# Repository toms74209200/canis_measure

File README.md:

<h1 style="text-align: center; margin-bottom: 4rem;">
<p style="font-size: 3rem;">Canis Measure</p>
Air Quality Monitor
</h1>

https://github.com/user-attachments/assets/3cffaff6-82ad-4612-b39e-0665e6a29b27

## Features

### Temperature and Humidity

Temperature and humidity sensor is the SHT30.

### Pressure, CO2

Pressure sensor is the BMP280, CO2 sensor is the MH-Z19B.

## Specification

- [Espressif ESP32-C6](https://www.espressif.com/en/products/socs/esp32-c6)
- [Sensirion SHT30](https://sensirion.com/products/catalog/SHT30-DIS-B)
- [BOSCH BMP280](https://www.bosch-sensortec.com/products/environmental-sensors/pressure-sensors/bmp280/)
- [Winsen MH-Z19B](https://www.winsen-sensor.com/product/mh-z19b.html)
- 128x64 OLED display(SSD1306)

### Schematic

https://github.com/toms74209200/canis_measure/blob/master/pcb/EAQM-250201.pdf

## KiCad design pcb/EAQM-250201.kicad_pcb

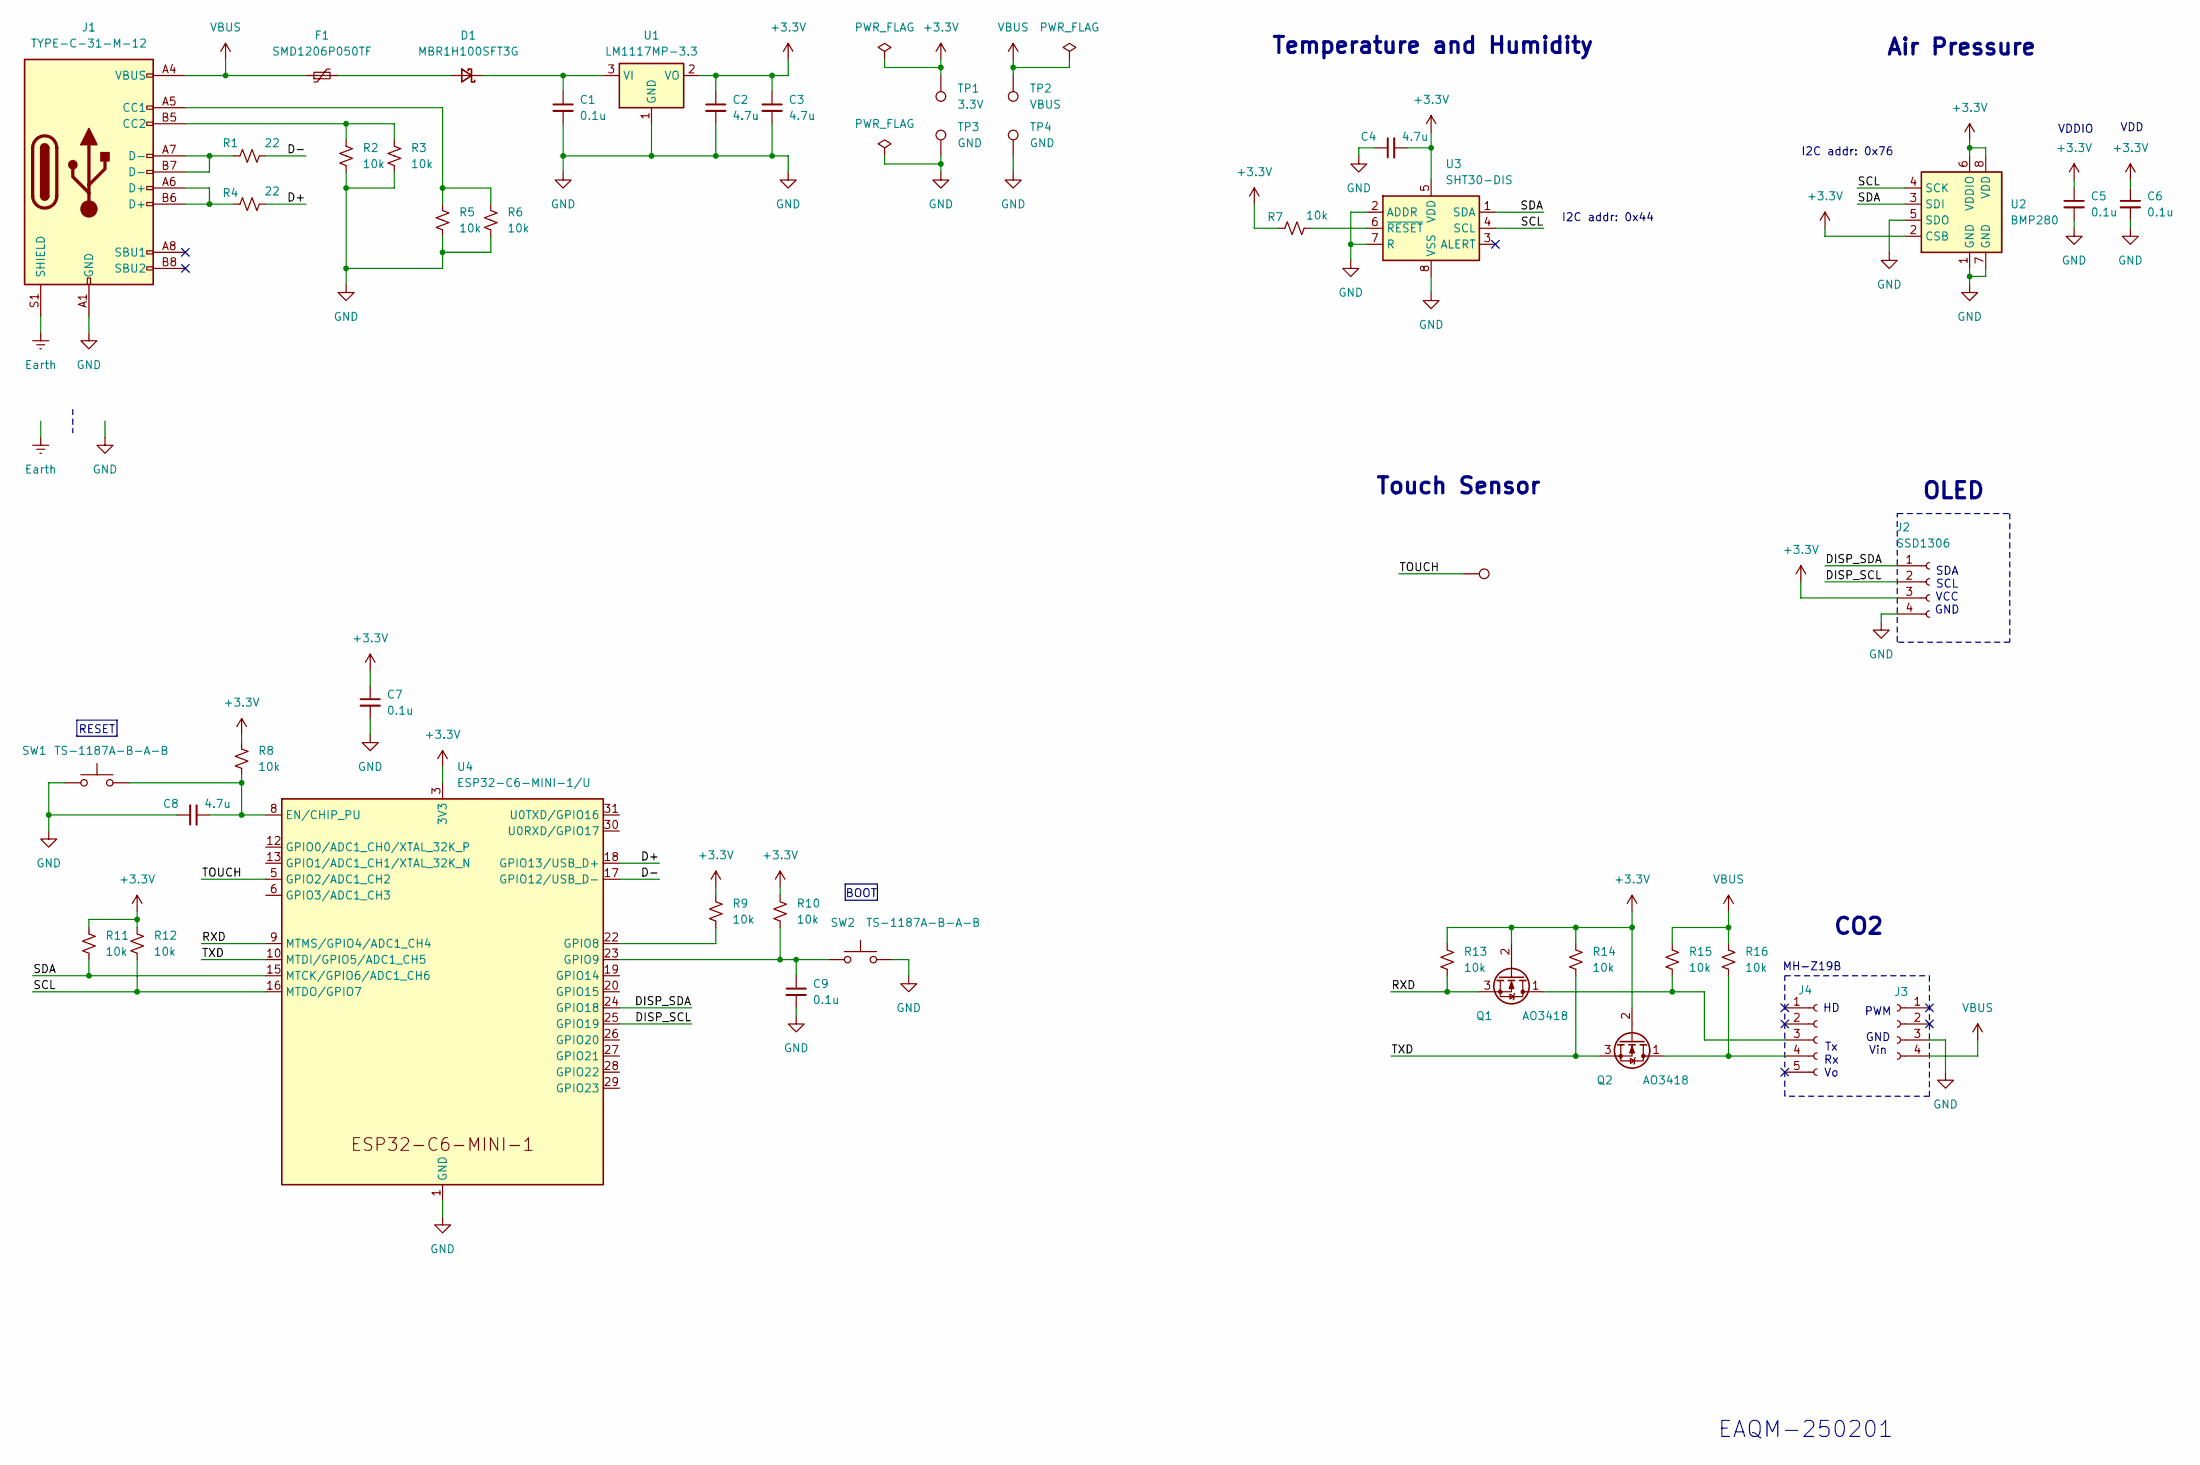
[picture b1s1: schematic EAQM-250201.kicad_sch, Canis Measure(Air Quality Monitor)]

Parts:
C1, C5, C6, C7, C9: 0.1u; C_0603_1608Metric
C2, C3, C4, C8: 4.7u; C_0603_1608Metric
D1: MBR1H100SFT3G; D_SOD-123F
F1: SMD1206P050TF; Fuse_1206_3216Metric
J1: TYPE-C-31-M-12; USB_C_Receptacle_Palconn_UTC16-G
J2: SSD1306; PinHeader_1x04_P2.54mm_Vertical
J3: Conn_01x04_Socket; PinHeader_1x04_P2.54mm_Vertical
J4: Conn_01x05_Socket; PinHeader_1x05_P2.54mm_Vertical
Q1, Q2: AO3418; SOT-23-3
R1, R4: 22; R_0603_1608Metric
R2, R3, R5, R6, R7, R8, R9, R10, R11, R12, R13, R14, R15, R16: 10k; R_0603_1608Metric
SW1, SW2: TS-1187A-B-A-B; SW_Push_1P1T_XKB_TS-1187A
TP1: 3.3V; TestPoint_Pad_D1.0mm
TP2: VBUS; TestPoint_Pad_D1.0mm
TP3, TP4: GND; TestPoint_Pad_D1.0mm
TP5: TestPoint
U1: LM1117MP-3.3; SOT-223-3_TabPin2
U2: BMP280; Bosch_LGA-8_2x2.5mm_P0.65mm_ClockwisePinNumbering
U3: SHT30-DIS; Sensirion_DFN-8-1EP_2.5x2.5mm_P0.5mm_EP1.1x1.7mm
U4: ESP32-C6-MINI-1/U; ESP32-C6-MINI-1

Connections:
+3.3V: C2.1, C3.1, C4.2, C5.1, C6.1, C7.1, J2.3, Q1.2 (G), Q2.2 (G), R7.1, R8.1, R9.1, R10.1, R11.1, R12.1, R13.1, R14.1, TP1.1, U1.2 (VO), U2.2 (CSB), U2.6 (VDDIO), U2.8 (VDD), U3.5 (VDD), U4.3 (3V3)
/D+: R4.2, U4.18 (GPIO13/USB_D+)
/D-: R1.2, U4.17 (GPIO12/USB_D-)
/DISP_SCL: J2.2, U4.25 (GPIO19)
/DISP_SDA: J2.1, U4.24 (GPIO18)
/RXD: Q1.3 (S), R13.2, U4.9 (MTMS/GPIO4/ADC1_CH4)
/SCL: R12.2, U2.4 (SCK), U3.4 (SCL), U4.16 (MTDO/GPIO7)
/SDA: R11.2, U2.3 (SDI), U3.1 (SDA), U4.15 (MTCK/GPIO6/ADC1_CH6)
/TOUCH: TP5.1, U4.5 (GPIO2/ADC1_CH2)
/TXD: Q2.3 (S), R14.2, U4.10 (MTDI/GPIO5/ADC1_CH5)
Earth: J1.S1 (SHIELD)
GND: C1.2, C2.2, C3.2, C4.1, C5.2, C6.2, C7.2, C8.1, C9.2, J1.A1 (GND), J1.A12 (GND), J1.B1 (GND), J1.B12 (GND), J2.4, J3.3, R2.2, R3.2, R5.2, R6.2, SW1.1, SW2.2, TP3.1, TP4.1, U1.1 (GND), U2.1 (GND), U2.5 (SDO), U2.7 (GND), U3.2 (ADDR), U3.7 (R), U3.8 (VSS), U3.9 (VSS), U4.1 (GND), U4.2 (GND), U4.11 (GND), U4.14 (GND), U4.36 (GND), U4.37 (GND), U4.38 (GND), U4.39 (GND), U4.40 (GND), U4.41 (GND), U4.42 (GND), U4.43 (GND), U4.44 (GND), U4.45 (GND), U4.46 (GND), U4.47 (GND), U4.48 (GND), U4.49 (GND), U4.50 (GND), U4.51 (GND), U4.52 (GND), U4.53 (GND)
unnamed: D1.2 (A), F1.2
unnamed: C1.1, D1.1 (K), U1.3 (VI)
unnamed: J1.A5 (CC1), R5.1, R6.1
unnamed: J1.B5 (CC2), R2.1, R3.1
unnamed: J1.A6 (D+), J1.B6 (D+), R4.1
unnamed: J1.A7 (D-), J1.B7 (D-), R1.1
unnamed: J4.3, Q1.1 (D), R15.2
unnamed: J4.4, Q2.1 (D), R16.2
unnamed: R7.2, U3.6 (~RESET)
unnamed: C8.2, R8.2, SW1.2, U4.8 (EN/CHIP_PU)
unnamed: R9.2, U4.22 (GPIO8)
unnamed: C9.1, R10.2, SW2.1, U4.23 (GPIO9)
VBUS: F1.1, J1.A4 (VBUS), J1.A9 (VBUS), J1.B4 (VBUS), J1.B9 (VBUS), J3.4, R15.1, R16.1, TP2.1

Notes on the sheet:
SDA SCL VCC GND
I2C addr: 0x44
Air Pressure
CO2
Temperature and Humidity
Touch Sensor
HD Tx Rx Vo
MH-Z19B
I2C addr: 0x76
BOOT
EAQM-250201
RESET
VDD
VDDIO
PWM GND Vin
OLED

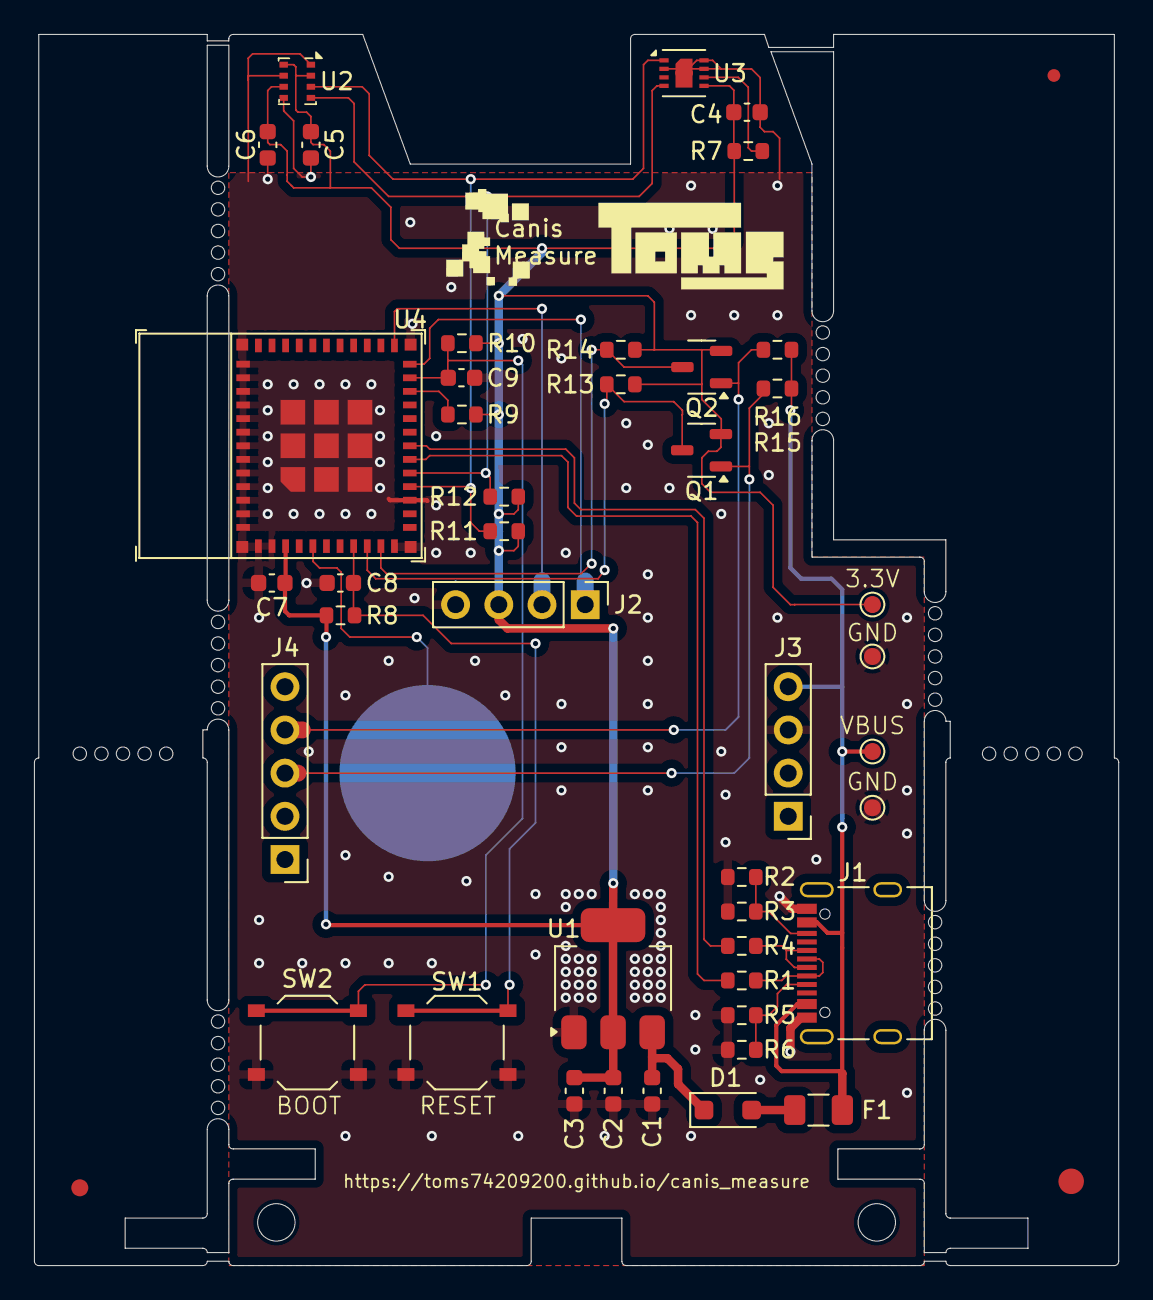
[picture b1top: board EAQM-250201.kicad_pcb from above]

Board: 2 copper layers, 63.8 x 72.4 mm, 43 parts (0 on the bottom side), 23 nets.

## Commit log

2025-02-08 :sparkles: Add schematic
2025-02-09 :sparkles: Update schematic
2025-02-09 :sparkles: Add document page
2025-02-09 :sparkles: Add PCB artwork
2025-02-09 :see_no_evil: Update gitignore
2025-02-11 :hammer: Add DevContainer settings for firmware
2025-02-11 :sparkles: Add project for firmware
2025-02-11 :hammer: Add editor settings for firmware
2025-02-12 :hammer: Update DevContainer settings
2025-02-13 :hammer: Add DevContainer settings for Arduino
2025-02-13 :hammer: Add editor settings for Arduino
2025-02-13 :sparkles: Add temperature sensor
2025-02-14 :sparkles: Update sleep method
2025-02-15 :sparkles: Add implementation for I2C controller
2025-02-15 :sparkles: Add Air Pressure sensor
2025-02-16 :sparkles: Add serial controller
2025-02-18 :sparkles: Add CO2 sensor
2025-02-19 :sparkles: Update I2C controller
2025-02-20 :sparkles: Add face image
2025-02-20 :sparkles: Update sleep
2025-02-22 :sparkles: Update serial controller implementation
2025-02-22 :bug: Update air pressure sensor
2025-02-22 :bulb: Add documention comments
2025-02-22 :art: Clean I2C controller
2025-02-22 :sparkles: Update CO2 sensor
2025-02-22 :hammer: Update editor settings
2025-02-23 :sparkles: Add Arduino main
2025-02-24 :memo: Update README
